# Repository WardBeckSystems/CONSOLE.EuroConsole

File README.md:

# EuroConsole

**A modular analog mixing console in Eurorack: Ward-Beck Systems circuits, digitally controlled, wired with Quad Twisted Pair.**

**Start here:** [`index.html`](index.html) walks through the whole console step by step. [`EDITOR/index.html`](EDITOR/index.html) builds your configuration as a KiCad schematic.

EuroConsole grows out of the 2016|49 *Digitally Controlled Analog Surround Sound Panner* (DCASSP), built at APK audio and Ward-Beck Systems as a Seneca College technology project. That prototype showed one idea: **the audio stays analog, the controls go digital**. Every control a mixer touches (encoders, buttons, faders, LEDs) is read by a microcontroller. The microcontroller sets digitally controlled analog parts, such as the Maxim DS1882 log-taper audio potentiometers, which do the actual work on the signal. Because the panel never carries audio, the controls can move, light up, recall and be driven remotely, and the signal path keeps the sound of the Ward-Beck circuits.

EuroConsole turns that prototype into a whole console, built from 3U Eurorack modules. The first build is the **C1616**:

| Part | What it is |
|---|---|
| **C1616 console** | 16 input channels (B300 Brain + F300 Fader strips) feeding **16 summing amplifiers**, in 4 rows of 6 modules |
| **Input** | M480B input module: the channel's mic/line front end |
| **4-input summing console** | one row: 4 × RJ45 QTP in (all 16 channels) → 4 summing amps, each with an insert point |
| **Processing** | EQ, compressor, de-esser, gate: patch into any insert |
| **Patch bay** | QTP patch bay module: inserts and buses on RJ45, normalled through |
| **Big VU Meter** (RD87) | the console's meter: the RD87 stereo Neopixel LED tower and its driver (REV 5, 2021\|54), plus moving-coil VU panels |

Everything connects with **QTP (Quad Twisted Pair)**: four balanced analog channels on one RJ45 / CAT5e cable, in the colour order **SUN, SKY, GRASS, EARTH**.

---

## How it fits together

```mermaid
flowchart LR
  subgraph CH["C1616: 16 channel strips"]
    direction TB
    B["B300 Brain<br/>input select · 4 aux · ESP32-S3"] --- F["F300 Fader<br/>POS pan · ONLY · SEL · fader · CH ON"]
  end
  IN["16 inputs<br/>(4 × QTP RJ45)"] --> M480["M480B input modules"] --> CH
  PB["QTP patch bay"] -.-|"normalled inserts and buses"| INS
  CH -->|"16 channels = 4 × QTP, to every row"| SUM
  subgraph SUM["Summing: 4 rows × (4 summing amps + insert + Big VU) = 16 summing amps"]
    direction TB
    Q["each row: 4 × RJ45 QTP in"] --> BUS["4 summing amps per row<br/>SUN · SKY · GRASS · EARTH"]
    BUS --> INS["insert point per bus<br/>send / return"]
  end
  INS <-->|"QTP send / return"| PROC
  subgraph PROC["Processing (any insert)"]
    direction TB
    EQ["EQ"] ~~~ COMP["Compressor"] ~~~ DES["De-esser"] ~~~ GATE["Gate"]
  end
  INS --> OUT["4 bus outputs (QTP)"]
  OUT --> DRV["Big VU Meter driver<br/>line in · MCU"] --> VU["Big VU Meter<br/>2 × 57 Neopixels"]
```

### Signal rules

- **Audio is analog and balanced end to end**: THAT 1246 line receivers in, THAT 1646 line drivers out. The 2016|49 prototype used these on every board.
- **Control is digital**: one ESP32-S3 per channel strip reads the panel and sets the gain parts. The modules talk to each other over I2C on the Eurorack bus, and the console talks to the outside world over the network. The 2016|49 prototype used Ethernet and the HUI protocol, run from an Arduino Mega.
- **Every interconnect is QTP**: one RJ45 carries four channels, so 16 outputs need only four cables. A QTP pair is also the insert send / return.

---

## 1. The C1616 console (16 × 16): channel strip = B300 + F300

**C1616** = 16 input channels × 16 summing amplifiers.

Each channel strip is two 6HP × 3U modules from the *HUI front panel REV 4.1* drawing ([DXF](MECHANICAL/HUI%20front%20panel%20REV%204.1.dxf)):

| B300 **Brain** (left) | F300 **Fader** (right) |
|---|---|
| INPUT LED and SEL button | **POS** encoder: position in the surround field (L · C · R · Ls · Rs) |
| SUN / SKY / GRASS / EARTH: four auxiliary controls, each with an encoder, a Neopixel and a push-button | **ONLY**: solo, isolate and cue |
| carries the channel's microcontroller | **SEL**: select, which draws attention to the channel |
| | 60 mm linear **fader** (Bourns PTA6043): channel level |
| | **CH ON**: channel on |

**Panning (from the 2016|49 theory of operation).** The POS encoder indexes a table of DS1882 settings, one per speaker, at 1 dB per step. Each speaker peaks at 63–64 steps, and neighbouring speakers cross at 48 steps (16 dB down):

```
{64,0,0,0,0} {48,48,0,0,0} {0,63,0,0,0} {0,48,48,0,0} {0,0,63,0,0} {0,0,48,48,0} {0,0,0,64,0} {0,0,0,48,48} {0,0,0,0,63}
```

The fader scales the looked-up row to a percentage. At power-up, every pot starts at full mute.

**C1616.** 16 input channels feed 16 summing amplifiers. The 16 channels leave the strips on four QTP cables (4 channels each), and every summing row receives all four. 16 strips × 12HP = 192HP, which is three rows of 84HP.

---

## 2. Summing: 4 rows of 6 = 16 summing amplifiers

The summing side is **4 rows of 6 modules**. Each row is one **4-input summing console**:

| Slot | Module |
|---|---|
| 1–4 | **summing amplifiers**: the row's four buses, SUN · SKY · GRASS · EARTH. All 16 channels arrive on the row's 4 × RJ45 QTP inputs |
| 5 | **insert / patch**: an insert send / return for each of the row's four buses (QTP) |
| 6 | **Big VU (RD87)**: meters the row's four buses |

4 rows × 4 = **16 summing amplifiers**: 16 inputs × 16 summing buses. Each bus has an **insert point** and leaves on a QTP output. *Slots 5 and 6 are provisional; the layout of 4 summing amps + 2 per row is set.* Big VU REV 5 shows two bars, so the row needs a 4-bar version, or two towers.

- **Summing amplifier:** Ward-Beck [M450](https://github.com/WardBeckSystems/MODULES.AMPLIFIERS.M450-Program-Summing-Amplifier) / [M450A](https://github.com/WardBeckSystems/MODULES.AMPLIFIERS.M450A-Program-Summing-Amplifier) / [M450B](https://github.com/WardBeckSystems/MODULES.AMPLIFIERS.M450B-Program-Summing-Amplifier) program summing amplifiers (Rodger Beck, 1975|8–1979|12). The 2016|49 prototype summed through 2 × 4 M450A cards. Also [M484 Dual Summing Amplifier](https://github.com/WardBeckSystems/MODULES.SUMMING.M484-Dual-Summing-Amplifier).
- **QTP backplane:** **QTP-BAC 14.1** (in `KICAD/`) is the four-channel QTP board, with RJ45s, transformers, XLR and BNC for SUN/SKY/GRASS/EARTH. It is the starting point for the summing console's input/output board.
- **Insert points:** a balanced send and return per bus, switched in or out. The model is the [M499 Insertion Switcher](https://github.com/WardBeckSystems/MODULES.UNSORTED.M499-Insertion-Switcher), plus the 1979|12 *M466N Insert Meter Module* drawing ([M466](https://github.com/WardBeckSystems/MODULES.DYNAMICS.M466-Limiter-Compressor-Module)). *Proposed:* sends on one RJ45 and returns on another, with QTP pairs 1–4 = buses 1–4, so one cable pair inserts a processor into all four buses.

---

## 3. Input: M480B

The [M480B input module](EAGLE/2021-APK/M480B%20Input%20module.sch) is the channel front end ahead of the B300/F300 strip. APK redrew it in Eagle in 2021|54 from the Ward-Beck original: LM201 op-amps, a MAT-01 matched pair and discrete output transistors (255 parts).

## 4. Processing: EQ, compressor, de-esser, gate

Each processor is a Eurorack module with QTP send / return, so it patches into any insert. Each one starts from a Ward-Beck circuit already drawn in this archive. Three already exist as 2021|54 APK Eagle redraws in [EAGLE/2021-APK](EAGLE/2021-APK/):

| Function | Starting from | Eagle (2021\|54 APK) | KiCad in the archive |
|---|---|---|---|
| **EQ** | [M462B Effects Equalizer](https://github.com/WardBeckSystems/MODULES.FILTERS.M462B-Equalizer-Module); also [M462](https://github.com/WardBeckSystems/MODULES.FILTERS.M462-Equalizer-Module), [M472](https://github.com/WardBeckSystems/MODULES.FILTERS.M472-Equalizer-Module) / [M472A](https://github.com/WardBeckSystems/MODULES.FILTERS.M472A-Stereo-Equalizer-Module) | `M462B Final.sch` (356 parts) | M462 27 · M462B 10 · M462C 11 · M472 14 · M472A 7 sheets |
| **Compressor** | [M466 Limiter-Compressor](https://github.com/WardBeckSystems/MODULES.DYNAMICS.M466-Limiter-Compressor-Module) (1976\|9): signal path, 6-106 control amplifier, output amplifier | `M466-compressor-limiter.sch` (315), `M466 - Control amp.sch` (114) | M466 15 · [M466M](https://github.com/WardBeckSystems/MODULES.DYNAMICS.M466M-Compressor-Meter-Module) 3 |
| **Output amplifier** (EQ and compressor) | the M466 / M462B output stage: LM201 and 4 complementary pairs | `M466 and M462B Output Amplifier.sch` (87) | in M466 |
| **De-esser** | M466 with a frequency-weighted (high-pass / band-pass) side-chain into its control amplifier | — | new circuit, based on M466 |
| **Gate** | [M467 Noise Gate and Meter Module](https://github.com/WardBeckSystems/MODULES.DYNAMICS.M467-Noise-Gate-and-Meter-Module) | — | M467 8 |

The front panels follow the B300/F300 language: encoders with Neopixels and POD buttons. The processor's ESP32-S3 sets its thresholds and gains through digitally controlled parts.

## 5. Patch bay

The **QTP patch bay module** puts every insert send / return and bus on RJ45, normalled through, so processors patch in with one CAT cable per four channels. It starts from **QTP-BITTREE PATCHBAY REV 2.1** (2021|54, Gerbers marked "good to go"): a 34 × 41 mm card with a top-row and bottom-row QTP RJ45, plugging into a Bittree patchbay connector, so a Bittree bay becomes a QTP bay. A sibling, **QTP-NEUTRIK D-hole** (24 × 27 mm), mounts a QTP RJ45 in a standard Neutrik D-hole for panels.

## 6. Metering: the Big VU Meter (RD87)

Big VU is Ward-Beck R&D project **RD87**, the *RD87 LED tower* (2015|48): a free-standing stereo level tower. Product repo: [PRODUCTS.BigVU](https://github.com/WardBeckSystems/PRODUCTS.BigVU). Page: [WBSps.ca Big VU](https://WBSps.ca/2026/PAGES/Big-VU.html). Simulator: [Big VU](https://WBSps.ca/2026/siumulation.html?plugin=bigvu), with front panel, tutorial, block diagram and firmware trace. In EuroConsole it is the console's meter bridge: one tower per bus pair, fed from the bus outputs.

- **VU meter driver + meter: Big VU Meter REV 5** (2021|54, 102 × 64 mm). A dual op-amp line input feeds an Arduino Micro, which drives two Neopixel bars of 57 pixels each (left / right). Two WBS 10-080 pots set the ceiling. The firmware ([SOFTWARE/BigVU](SOFTWARE/BigVU/), 2015|48) adds a log scale, calibration and two falling peak dots. This is the driver to move to Eurorack and the ESP32-S3.
- **Moving-coil VU meters**, one per bus, as in the 2016|49 prototype (five WBS meters, each with a 15 dB calibration pad): [M435 VU Meter](https://github.com/WardBeckSystems/MODULES.METER.M435-VU-Meter), driven by an [M405 Extended Range VU Meter](https://github.com/WardBeckSystems/MODULES.METER.M405-Extended-Range-VU-Meter) / [M445](https://github.com/WardBeckSystems/MODULES.METER.M445-Extended-Range-Meter) stage (+4 dBu = 0 VU).

---

## Console editor: configuration → KiCad schematic

[`EDITOR/index.html`](EDITOR/index.html) is an interactive page that builds a specific console and writes its KiCad 9 schematic. Open it in a browser; it works offline from the file.

- **Every Eurorack module is a bank of 4 channels** (one QTP in / out): quad preamp (4 preamp sections + 4 vertical VU), EQ, compressor, de-esser, send banks and faders, 24HP, drawn to Eurorack scale with the master section in the middle.
- **Summing in the send banks:** each send bank (Aux 1-4, Aux 5-8, M 1-4) takes two 4-channel inputs, PRE (the insert return, before the fader) and POST (the fader out), sets every send pre or post, sums its 4 channels per bus inside the module with the bus coming in from the previous bank, and passes the bus on to the next bank, then the master (insert, compressor, fader, Big VU). No summing point takes more than 5 inputs. Every bank also has a pre-fader and a post-fader QTP out. Separate summing amps are set aside for now.
- **Digitally controlled analog:** every parameter is a DS1882 wiper or a digital switch under a control layer (an ESP32-S3 per bank on I2C). The editor counts the parameters, DS1882s, I2C expanders and I2C buses.
- **Power:** a first estimate per module on +12 V, −12 V and +5 V, per rack row and in total, with the supplies needed and a power-flow diagram (to be measured).
- **Summing rows:** each summing amp is a bus named by what it sums: M1–M4, AUX1–AUX8, then direct sums (BUS13…). The C1616 is rows M1–4 · AUX1–4 · AUX5–8 · BUS13–16, each with insert and Big VU. The name follows the configuration: 16 inputs × 16 summing amps = **C1616**.
- **Download:** a zip of a hierarchical KiCad 9 project: a root sheet, a channels sheet and one sheet per summing row. It includes `EuroConsole.kicad_sym` and `sym-lib-table`, plus the configuration (JSON, which *Load config* reads back) and a parts list (CSV).
- **Symbols:** the Ward-Beck modules use the archive's own symbols (`2026/Engineering/KICAD`: M480B, M450, M499, M462B, M466, M467), with their real card-edge pins. QTP RJ45, XLR, the B300/F300 strip and the RD87 Big VU are EuroConsole parts. Run `python3 EDITOR/build_symbols.py` to refresh `symbols.js`.
- **Nets** are global labels shared by every sheet: `IN` (XLR), `FS`/`FR` (M480B fader send / return through the strip), `CH` (channels on QTP), `SUMN` (summing nodes), `SEND`/`RET` (inserts), `BUS` (bus outputs) and `P<ref>_` (processor patch points). QTP pairs are SUN 2/1 · SKY 4/5 · GRASS 6/3 · EARTH 8/7, with the shell to GND.
- **Tested:** `node EDITOR/test_generator.js` generates the C1616, has `kicad-cli` load it, and checks the netlist. Each summing node has its 16 resistors plus the M450 input; each channel reaches its 16 resistors and all four rows. ERC leaves only "power pin not driven" (the schematic has no supply). The archive's M462B, M466 and M467 symbols give left and right the same pin numbers, so ERC reports duplicate pins when those modules are placed.

## Reference: Boredbrain Xcelon

The [Boredbrain Music Xcelon](https://www.chicagomusicexchange.com/en-ca/blogs/news/boredbrain-music-xcelon-eurorack) (CA$1,372) is the closest commercial Eurorack mixer: an all-analog six-channel stereo mixer in one module. Its features, against EuroConsole:

| Xcelon | EuroConsole |
|---|---|
| Six stereo / dual-mono channels, low-noise analog | banks of 4 mono channels per module; balanced +4 dBu on QTP; Ward-Beck circuits |
| Two stereo FX sends, two FX returns | Aux 1-4 and Aux 5-8 send banks (8 sends); returns through the insert / patch bay |
| Two stereo mix buses, selectable per channel | M 1-4 send bank onto the M1-M4 masters; direct sums |
| Variable input gain for modular and line-level sources | quad preamp (M480 / M460 / M470 / M441): mic or line; **planned:** a Eurorack-level input setting |
| Long-travel faders with CV-responsive LEDs | F300 fader bank (60 mm Bourns) with Neopixels |
| Balance with pan law; dual-mono crossfade mode | F300 POS pan on the DS1882 pan-law table; **planned:** crossfade mode |
| Clickless mutes, VU meters on all channels | CH ON; the DS1882's zero-crossing detector switches without clicks; quad preamp meters and Big VU on every bus |
| 26 CV inputs | **planned:** CV in per channel (volume 0 to +5 V, pan ±5 V, sends), read by the bank's ESP32-S3 |
| Jumpers: pre/post-fader FX and meters, volume VCA mode | send taps are post-fader (in software, settable per bank, **planned**); every level is a DS1882, so a VCA mode is a firmware setting |
| Expansion ports: channel expanders, direct outs | every bank is a module; every channel already leaves on QTP (direct out) |

## Reference: XAOC Devices Praga

The **XAOC Devices Praga** (*1967 Voltage Controlled Stereo Mixing Console*) is a Eurorack mixer laid out the way EuroConsole lays out every module: **a bank of 4 channels in one module**. From its front panel, each channel has a large VOL knob, an ACTIVE / MODE button with a status LED, PAN, an AUX knob between sends A and B, a **5-segment vertical LED meter**, and jacks for INPUT, VCA OUT and PAN / VOL CV; the shared row carries AUX SEND / RETURN A and B and the STEREO SUM L / R.

| Praga | EuroConsole |
|---|---|
| 4 channels per module | every module is a bank of 4 channels (24HP, one QTP in and out) |
| a vertical LED meter per channel | the quad preamp's vertical VU per channel; Big VU on every bus |
| PAN and VOL CV per channel | **planned** (see the Xcelon: CV in, read by the bank's ESP32-S3) |
| AUX knob between sends A and B | the send banks: Aux 1-4, Aux 5-8, M 1-4 |
| VCA OUT per channel | every channel leaves on QTP (direct out) |
| stereo sum on the module | summing stays in its own modules: group sums of 8 with their channels, the Σ in the master |

## Reference: WMD Performance Mixer MKII

The **WMD Performance Mixer MKII** (US$2,205; PM Channels MKII US$955, PM DB25 MKII US$440, PM MKII Returns US$205) is the most console-like of the three: eight stereo channels, expanding **four channels at a time** up to 24.

| Performance Mixer MKII | EuroConsole |
|---|---|
| Expands 4 channels at a time (PM Channels MKII), up to 24 | every module is a bank of 4; channels in fours, 4 to 64 |
| DB25 MKII: balanced line-level outs, pre- or post-fader, per 4 channels | every bank leaves on QTP (4 balanced channels per RJ45); **planned:** pre / post choice |
| Gain −12 to +20 dB, clip LED 1 dB before clipping | quad preamp gain; **planned:** a clip LED per channel |
| Soft mute (no click) | CH ON through the DS1882's zero-crossing switch |
| Pan or crossfade per channel; CV sums with the pot | F300 POS pan; **planned:** crossfade mode and CV in |
| Faders as VCAs (Level CV in VCA mode) | every level is a DS1882 set by the ESP32-S3: a VCA mode is firmware |
| AUX1 post, AUX2 pre or post | Aux 1-4 / Aux 5-8 send banks, post-fader; **planned:** pre / post per bank |
| Cue and Bus: master only, master + bus, bus only | ONLY (solo / cue) on the F300; M 1-4 send bank onto the M1-M4 masters |
| Groups: 8 mute / bus / cue snapshots recalled with one hand | **planned:** snapshots in the ESP32-S3s (the controls are all digital already) |
| Master insert; Mix In after the insert; Aux returns before it | insert on every master bus (M499 + QTP send / return); **planned:** a Mix In after the master insert |
| Balanced stereo master out, LED VU | QTP bus outs; Big VU on every bus |
| Replaceable channel strips; patchbay, power and master as separate assemblies | every bank module is replaceable by itself |
| Expansion headers 2.0 mm shrouded, cannot be plugged into power | **planned:** keyed inter-module connectors that cannot meet the Eurorack 16-pin power |

**From the manual** (WMD, *Performance Mixer MKII*):

| | Performance Mixer MKII | PM Channels MKII (4 ch) | DB25 MKII |
|---|---|---|---|
| Width | 52HP | **24HP** | 4HP |
| Power | +620 / −560 mA (to ±750 mA when distorting) | +320 / −280 mA (to ±350 mA) | ±150 mA |
| Inputs | 20 kΩ; HPF −3 dB at 10 Hz; gain −12 to +20 dB | same | — |
| Faders / aux | −100 to +5 dB; level / aux CV 0 to 5 V (100 kΩ); pan CV ±5 V (200 kΩ) | same | — |
| Outputs | master balanced 3.5 mm TRS, 600 Ω, DRV135; others 1 kΩ modular level | 1 kΩ modular level | 16 × DRV135, balanced 600 Ω, **+4 dBu nominal**, THD+N < 0.1 %, TASCAM DB25 |
| Pan law | −3 dB centre, −100 / 0 dB hard pan | same | — |
| Response | ±0.5 dB 20 Hz–20 kHz; L/R within ±0.5 dB; every point phase-correct | same | — |

Also from the manual:
- Each OUTS header is 2 mm, 16-pin: four stereo channels, signal on the even pins and ground on every odd pin.
- Each INSERT header is 8-pin: send / return left and right, post-gain and pre-fader, with jumpers when unused.
- MIDI: CC 32 upward, 4 per strip (level, pan, aux 1, aux 2).
- 8 group snapshots of mute, bus and cue.
- Firmware loads from an SD card.

**What it tells EuroConsole:**
- **Width:** a bank of 4 at 24HP is what WMD ships for 4 channels (PM Channels MKII).
- **Power:** about +320 / −280 mA per 4-channel module is a realistic budget to check our banks against on ±12 V.
- **Balanced outs:** WMD's DB25 uses DRV135 drivers at +4 dBu. Our THAT 1646 drivers do the same job on QTP.
- **Internal ribbons:** ground on every other conductor between modules.
- **Inserts:** an insert point on every channel, post-gain and pre-fader, beside the master insert.
- **Firmware:** the ESP32-S3s can send the same kind of MIDI CC overlay for DAW automation, and keep group snapshots.

## Boards in this repo

`KICAD/` holds KiCad 9 boards converted from the Eagle designs in `EAGLE/` with [`tools/eagle2kicad_pcb.py`](https://github.com/WardBeckSystems/WBSps.ca/blob/main/tools/eagle2kicad_pcb.py). `KICAD/split_boards.py` splits the combined 2016|49 Eagle sheet into one board per module. Each board is placed in its panel's coordinates, with the panel drawing on *User.Drawings*.

| Board | From | Size | Parts | Panel check |
|---|---|---|---|---|
| `B300_Front` | 2016\|49 Encoder PCB 17.2 | 30 × 113.6 mm | 37 | all 14 controls within 0.18 mm of their panel holes (4 Neopixels + INPUT LED, 4 encoder holes, 5 buttons) |
| `F300_Fader` | 2016\|49 Encoder PCB 17.2 | 30 × 113.6 mm, L-shape | 14 | ONLY, SEL and CH ON within 0.01 mm; the fader's 4 mounting pads within 0.02 mm of the panel screws; the POS encoder mounts on the panel above the notch |
| `B300_Main` | 2016\|49 Encoder PCB 17.2 | 133.8 × 113.4 mm | 27 | perpendicular side board: 4 encoders (WBS 10-081), Arduino Mega, RS-485, DB9, DS1808 |
| `Maxim_Adapter_Board` | 2016\|49 Maxim Adapter Board | 20 × 25 mm | 3 | DS1882 breakout (also on the Encoder sheet) |
| `QTP-BAC_14.1` | 2016\|49 | 114 × 50 mm | 112 | four-channel QTP backplane: RJ45, transformers, XLR, BNC |
| `Big_VU_Meter_REV5` | 2021\|54 APK | 102 × 64 mm | 84 | stereo Neopixel VU meter and driver |
| `QTP-BITTREE_Patchbay_REV2.1` | 2021\|54 APK | 34 × 41 mm | 10 | QTP card for a Bittree patchbay |
| `QTP-NEUTRIK_D-hole` | 2021\|54 APK | 24 × 27 mm | 7 | QTP RJ45 in a Neutrik D-hole |
| `Encoder_PCB_17.2` | 2016\|49 | — | 221 | the whole Eagle sheet, kept as the source |

| B300 Front | F300 Fader | Big VU Meter | QTP Bittree patchbay |
|---|---|---|---|
|  |  |  |  |

**Schematics.** The Eagle `.sch` files (M480B, M462B, M466, the output amplifier, the VU meter, the patchbay, and the 2016|49 DCASSP sheets) still need KiCad's GUI importer: File → Import → Non-KiCad Schematic. The 2016|49 schematics are also in [MANUALS/2016 - DCASSP schematics V1.pdf](MANUALS/2016%20-%20DCASSP%20schematics%20V1.pdf).

## Roadmap

- **From the Xcelon, the Praga and the WMD Performance Mixer MKII:** CV inputs per channel (volume, pan, sends) read by each bank's ESP32-S3; a Eurorack-level input setting and a clip LED per channel on the quad preamp; pan crossfade mode; pre / post-fader sends and direct outs per bank; mute / bus / cue snapshots; a Mix In after the master insert; keyed inter-module connectors that cannot meet power.

1. **B300 / F300 for Eurorack**: replace the Arduino Mega side board with an ESP32-S3 on the B300, and connect the F300 by ribbon. Use the Eurorack 16-pin power header (±12 V, regulated to ±7 V for the DS1882 analog rails). Connect modules over I2C.
2. **Input**: M480B as a Eurorack input module.
3. **Summing console**: a 4 × QTP input board from QTP-BAC, an M450-style summing amplifier per bus, and an insert send / return per bus.
4. **Processing**: EQ (M462B), compressor (M466), de-esser (M466 side-chain), gate (M467). Each gets a Eurorack PCB and panel with QTP send / return, sharing the M466/M462B output amplifier.
5. **Patch bay**: QTP-BITTREE and QTP-NEUTRIK into a Eurorack QTP patch module, normalled.
6. **Metering**: Big VU Meter onto the ESP32-S3 as the VU meter driver, plus moving-coil VU panels.
7. **The C1616 frame**: three 84HP rows, the power, the QTP patch, and network control.

## Source material

| Folder | What |
|---|---|
| [EAGLE/2016-DCASSP](EAGLE/2016-DCASSP/) | Encoder PCB 17.2, QTP-BAC 14.1, Maxim (DS1882) adapter, VU meter and summing amp, block diagram |
| [EAGLE/2021-APK](EAGLE/2021-APK/) | M480B, M462B, M466, M466 control amp, M466/M462B output amp, Big VU Meter REV 5, QTP-BITTREE patchbay, QTP-NEUTRIK D-hole |
| [GERBERS/](GERBERS/) | QTP-BITTREE PATCHBAY REV 2.1 ("good to go") |
| [SOFTWARE/](SOFTWARE/) | DCASSP channel-strip firmware (Arduino Mega, 2016) with its history, pan law and PC interface; Big VU meter firmware (all versions), which runs every vertical meter |
| [MANUALS/](MANUALS/) | 2016\|49 DCASSP final report (TPJ655) and schematics |
| [MECHANICAL/](MECHANICAL/) | HUI front panel REV 4.1 (DXF and render), Bourns PTA6043 fader |
| [PHOTOS/](PHOTOS/) | HUI prototype cross reference |

---
© Ward-Beck Systems (Ward-Beck.com - Ward-Beck.ca) · DCASSP design and archive by Anthony Peter Kuzub · [WBSps.ca](https://WBSps.ca) · [WBSps.Kuzub.com](https://WBSps.Kuzub.com)

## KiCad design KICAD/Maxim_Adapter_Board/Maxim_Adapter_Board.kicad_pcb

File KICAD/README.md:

# EuroConsole boards (KiCad 9)

| Board | Rev | What it is | From |
|---|---|---|---|
| [B300 Brain - front PCB](B300_Front/) | 17.2 | Neopixels, POD buttons, encoder shaft holes; placed on the HUI front panel REV 4.1 | Encoder PCB REV 17.2 (2016 DCASSP) |
| [B300 Brain - main side board](B300_Main/) | 17.2 | 4 encoders (WBS 10-081), Arduino Mega, RS-485, DB9, DS1808; perpendicular to the panel | Encoder PCB REV 17.2 (2016 DCASSP) |
| [F300 Fader - fader PCB](F300_Fader/) | 17.2 | Bourns PTA6043 fader, ONLY / SEL / CH ON buttons; placed on the HUI front panel REV 4.1 | Encoder PCB REV 17.2 (2016 DCASSP) |
| [DS1882 adapter](DS1882_Adapter/) | 17.2 | Maxim DS1882 dual log digital potentiometer breakout | Encoder PCB REV 17.2 (2016 DCASSP) |
| [QTP-BAC - four-channel QTP backplane](QTP-BAC_14.1/) | 14.1 | SUN SKY GRASS EARTH on RJ45: transformers, XLR, BNC, euro blocks | QTP-BAC 14.1 (2016 DCASSP) |
| [Big VU (RD87) - meter and driver](Big_VU_Meter_REV5/) | 5 | stereo line in, Arduino Micro, 2 x 57 Neopixel towers | Big VU meter REV 5 (2021 APK) |
| [QTP-BITTREE - patchbay card](QTP-BITTREE_Patchbay_REV2.1/) | 2.1 | top-row and bottom-row QTP RJ45 on a Bittree patchbay connector | QTP-BITTREE PATCHBAY REV 2.1 (2021 APK) |
| [QTP-NEUTRIK - D-hole RJ45](QTP-NEUTRIK_D-hole/) | 1 | QTP RJ45 in a Neutrik D-hole | QTP-NEUTRIK D-hole (2021 APK) |
| [Encoder PCB - 2016 DCASSP sheet (source)](Encoder_PCB_17.2/) | 17.2 | the whole Eagle sheet: every board above plus documentation frames | Encoder PCB REV 17.2 (2016 DCASSP) |

Each board carries its name in the title block. `split_boards.py` splits the Encoder sheet per module in panel coordinates; `name_boards.py` writes these names.

## Schematics

Every Eagle schematic in `EAGLE/` is converted with KiCad's own importer (eeschema, File → Import → Non-KiCad Schematic), driven on a virtual display because `kicad-cli` has no schematic import: `tools/eagle_sch_batch.py` (Xvfb `:77`, a fresh eeschema per file; `xdrv.py` clicks / keys, `xclip_owner.py` hands the path to the file dialog). Each converted schematic sits next to its board where there is one, with its `*-eagle-import.kicad_sym` and `sym-lib-table`.

| Schematic | Parts | Nets |
|---|---|---|
| Encoder_PCB_17.2 (11 sheets) | 173 | 278 |
| M462B_EQ | 268 | 224 |
| M466_Compressor_Limiter | 231 | 191 |
| M480B_Input_Module | 205 | 187 |
| M466_Control_Amp | 82 | 60 |
| Big_VU_Meter_REV5 | 80 | 79 |
| M466_M462B_Output_Amplifier | 73 | 50 |
| QTP-BAC_14.1 | 68 | 43 |
| VU_Meter_Summing_Amp_rev1 | 22 | 59 |
| QTP-BITTREE_Patchbay_REV2.1 | 10 | 45 |
| QTP-NEUTRIK_D-hole | 8 | 17 |
| Block_Diagram_v2 | 6 | 10 |
| Maxim_Adapter_Board | 3 | 16 |

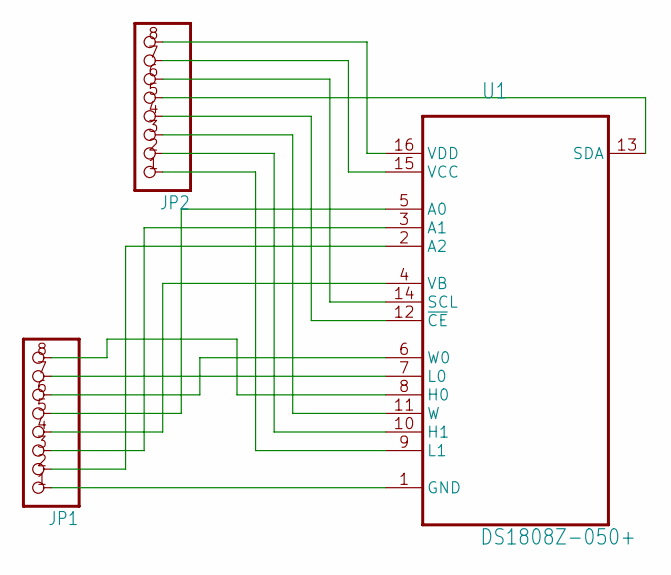
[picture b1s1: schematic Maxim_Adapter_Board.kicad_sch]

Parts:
JP1, JP2: PINHD-1X8; 1X08
U1: DS1808Z-050+; SOIC127P600X175-16N

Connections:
unnamed: JP1.1, U1.1 (GND)
unnamed: JP1.2, U1.2 (A2)
unnamed: JP1.3, U1.3 (A1)
unnamed: JP1.4, U1.4 (VB)
unnamed: JP1.5, U1.5 (A0)
unnamed: JP1.6, U1.6 (W0)
unnamed: JP1.7, U1.7 (L0)
unnamed: JP1.8, U1.8 (H0)
unnamed: JP2.1, U1.9 (L1)
unnamed: JP2.2, U1.10 (H1)
unnamed: JP2.3, U1.11 (W)
unnamed: JP2.4, U1.12 (~CE)
unnamed: JP2.5, U1.13 (SDA)
unnamed: JP2.6, U1.14 (SCL)
unnamed: JP2.7, U1.15 (VCC)
unnamed: JP2.8, U1.16 (VDD)

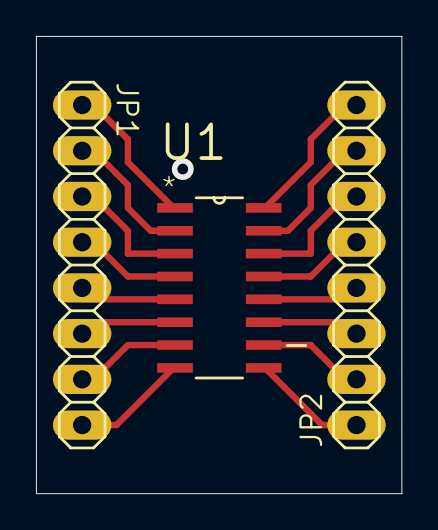
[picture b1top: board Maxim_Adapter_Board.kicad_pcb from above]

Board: 2 copper layers, 20.3 x 25.4 mm, 3 parts (0 on the bottom side), 16 nets.

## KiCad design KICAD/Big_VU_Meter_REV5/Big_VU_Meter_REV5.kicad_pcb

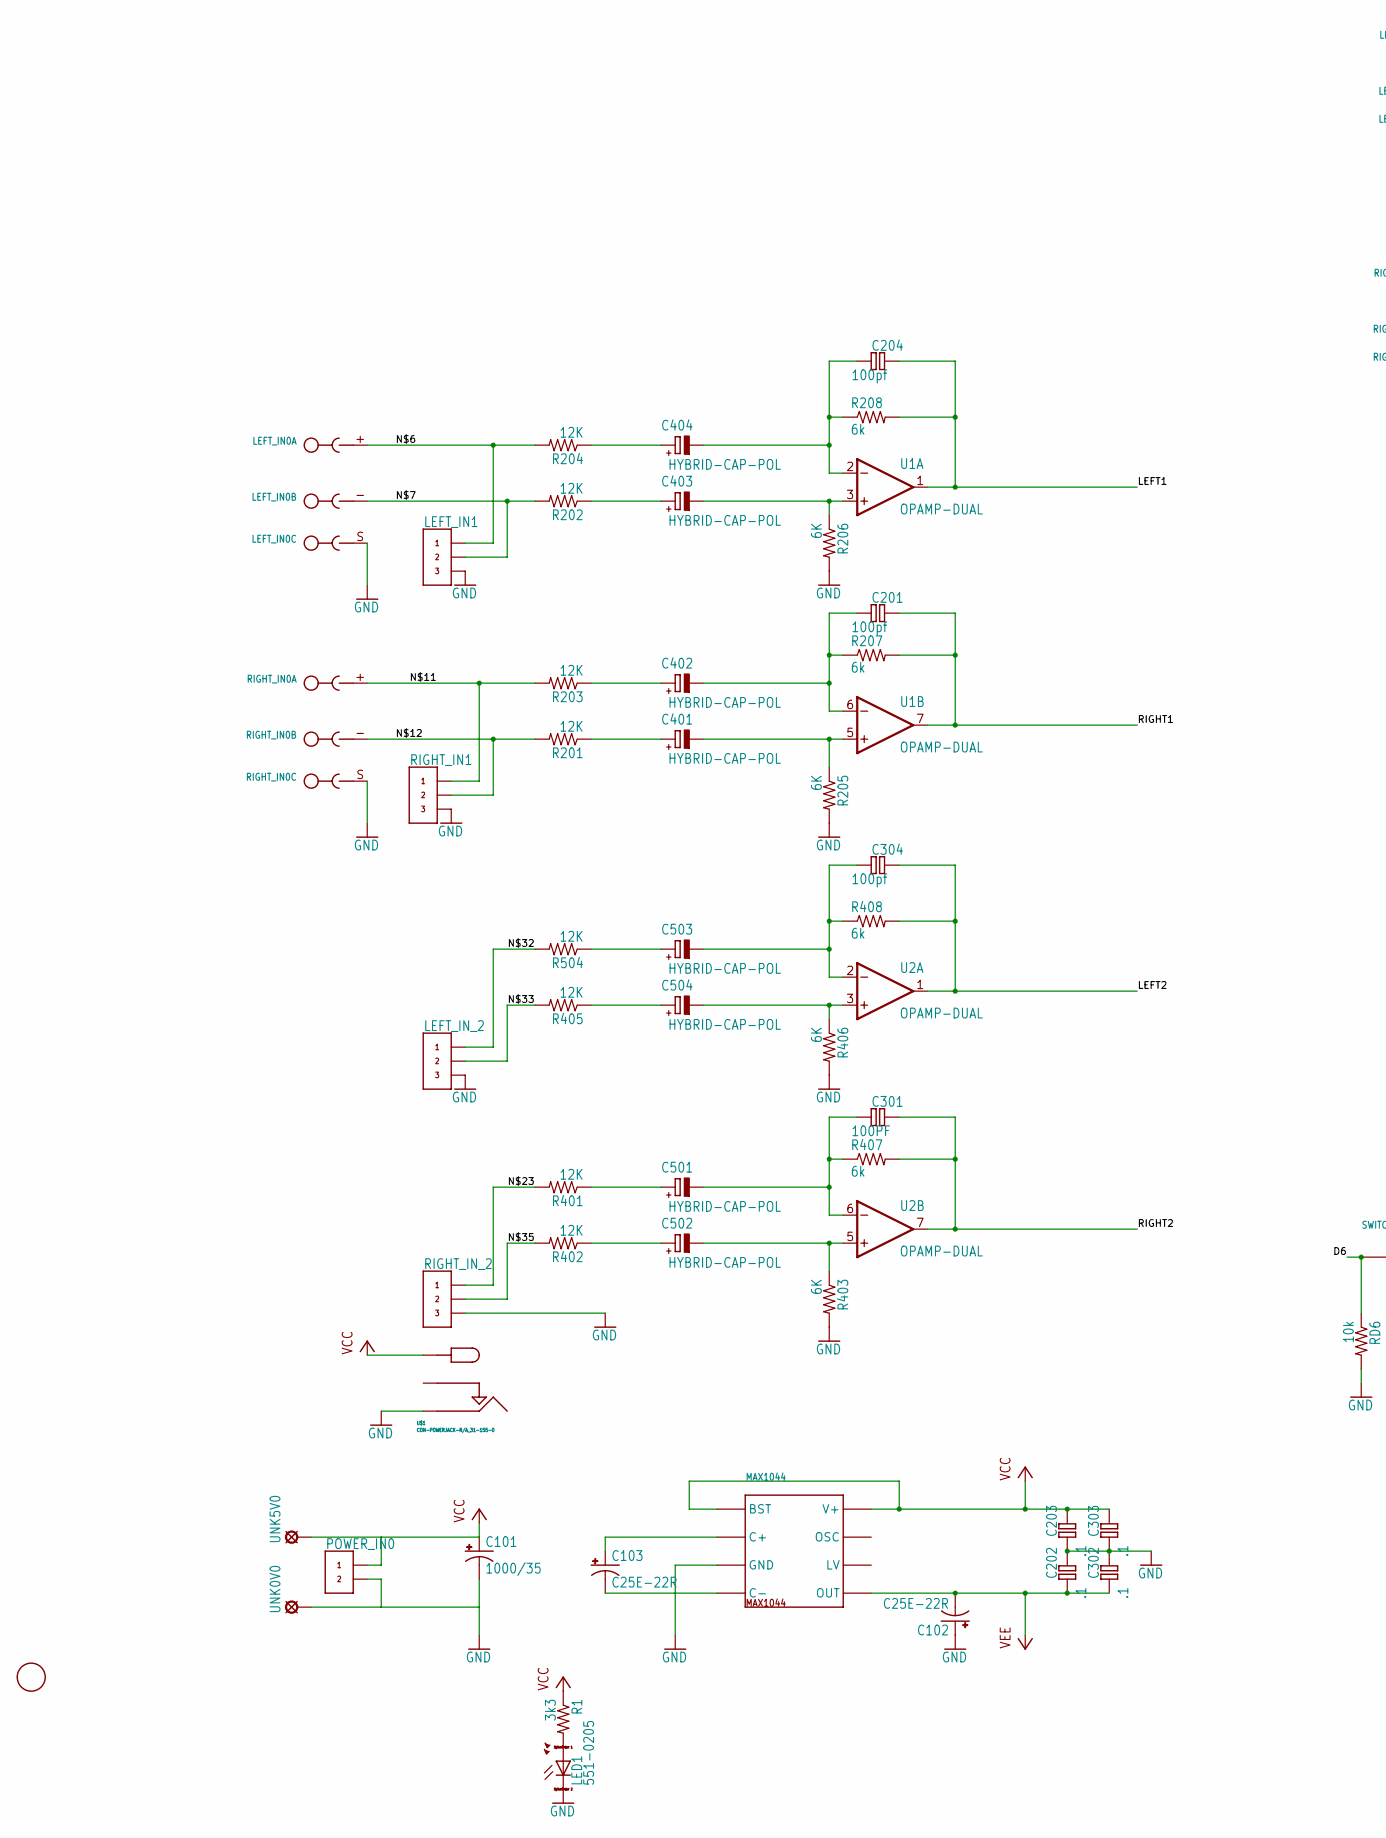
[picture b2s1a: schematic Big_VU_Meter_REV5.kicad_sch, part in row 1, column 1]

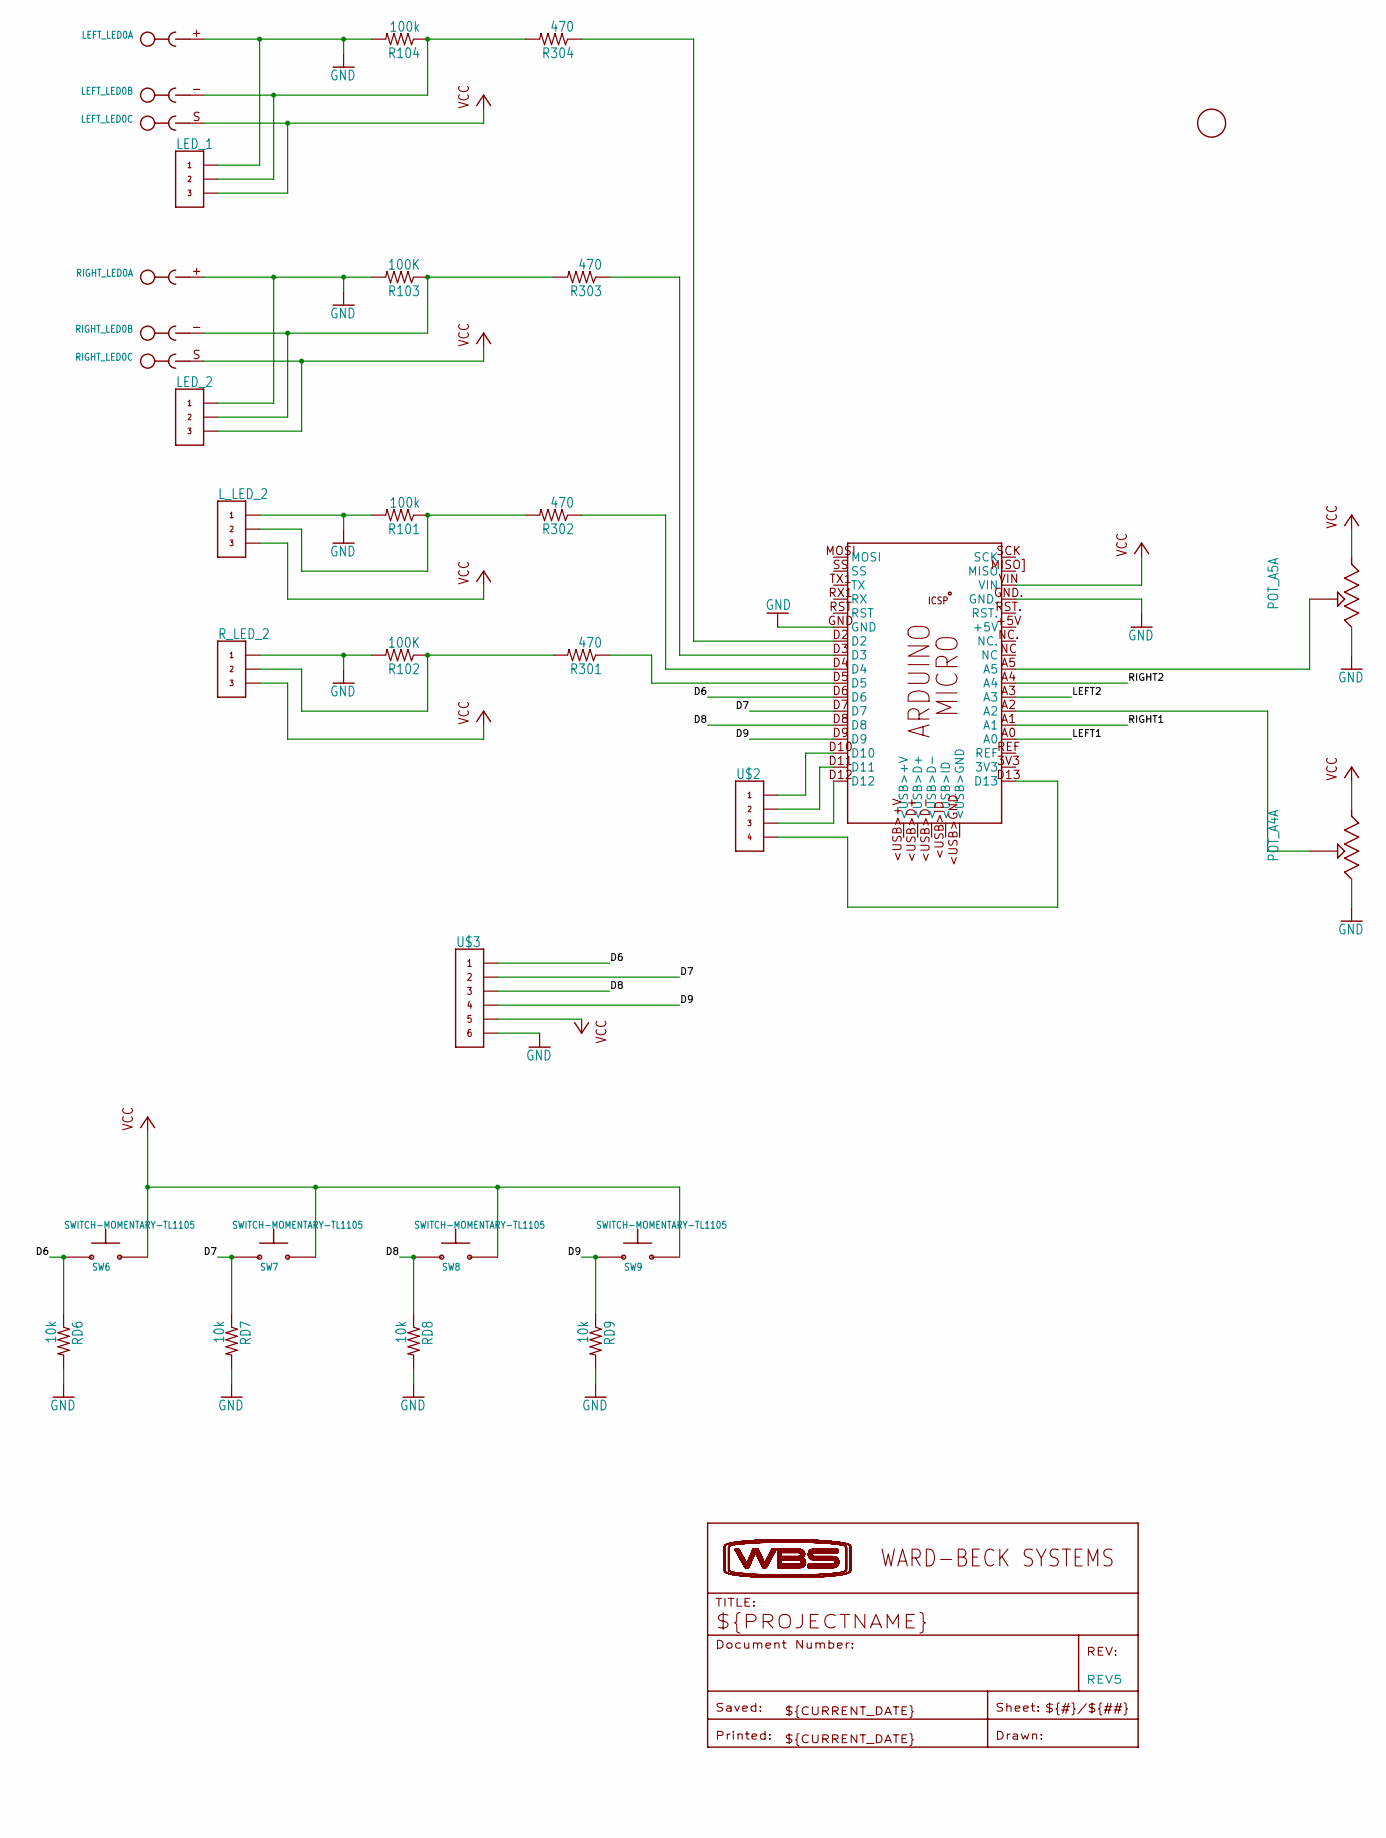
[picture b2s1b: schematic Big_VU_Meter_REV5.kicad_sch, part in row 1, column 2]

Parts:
C101: 1000/35; E5-5
C102, C103: C25E-22R; E2,5-6
C201, C204, C304: 100pf; HYBRID-CAP-CERAMIC-1206
C202, C203, C302, C303: .1; HYBRID-CAP-CERAMIC-1206
C301: 100PF; HYBRID-CAP-CERAMIC-1206
C401, C402, C403, C404, C501, C502, C503, C504: HYBRID-CAP-POL; HYBRID-CAP-TANT
LED1: 551-0205; LED_LD260
LED_1, LED_2: CON-WBS-LOCKING-0.1-3
LEFT_IN0: CON-PHOENIX_RIGHT_ANGLE_3.81; CON-PHOENIX_MC1.5_3-G-3.81
LEFT_IN1: CON-WBS-LOCKING-0.1-3
LEFT_IN_2: CON-WBS-LOCKING-0.1-3
LEFT_LED0: CON-PHOENIX_RIGHT_ANGLE_3.81; CON-PHOENIX_MC1.5_3-G-3.81
L_LED_2: CON-WBS-LOCKING-0.1-3
MAX1044: MAX1044; DIP8
PCB1: ARDUINO_MICRO
POT_A4, POT_A5: 10-080; WBS_079
POWER_IN0: CON-WBS-LOCKING-0.1-2
R1: 3k3; HYBRID-RESISTOR-1206-0.3
R101, R104: 100k; HYBRID-RESISTOR-1206-0.3
R102, R103: 100K; HYBRID-RESISTOR-1206-0.3
R201, R202, R203, R204, R401, R402, R405, R504: 12K; HYBRID-RESISTOR-1206-0.3
R205, R206, R403, R406: 6K; HYBRID-RESISTOR-1206-0.3
R207, R208, R407, R408: 6k; HYBRID-RESISTOR-1206-0.3
R301, R302, R303, R304: 470; HYBRID-RESISTOR-1206-0.3
RD6, RD7, RD8, RD9: 10k; HYBRID-RESISTOR-1206-0.3
REV5: WBS-DOCUMENT_INFO_FRAME; WBS-FRAME_PCB
RIGHT_IN0: CON-PHOENIX_RIGHT_ANGLE_3.81; CON-PHOENIX_MC1.5_3-G-3.81
RIGHT_IN1: CON-WBS-LOCKING-0.1-3
RIGHT_IN_2: CON-WBS-LOCKING-0.1-3
RIGHT_LED0: CON-PHOENIX_RIGHT_ANGLE_3.81; CON-PHOENIX_MC1.5_3-G-3.81
R_LED_2: CON-WBS-LOCKING-0.1-3
SW6, SW7, SW8, SW9: SWITCH-MOMENTARY-TL1105; SWITCH-TACT_TL1105
U1, U2: OPAMP-DUAL; DIP8
U$1: CON-POWERJACK-R/A_31-155-0; CON-POWERJACK-R_A_31-155-0
U$2: CON-WBS-LOCKING-0.1-4
U$3: CON-WBS-LOCKING-0.1-6
U$4, U$5: FIDUCIAL; FIDUCIAL_1MM
UNK0V0, UNK5V0: LSP13

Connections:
D6: PCB1.D6, RD6.1, RD6.1A (1), SW6.P$1 (1), SW6.P$2 (1), U$3.P$1
D7: PCB1.D7, RD7.1, RD7.1A (1), SW7.P$1 (1), SW7.P$2 (1), U$3.P$2
D8: PCB1.D8, RD8.1, RD8.1A (1), SW8.P$1 (1), SW8.P$2 (1), U$3.P$3
D9: PCB1.D9, RD9.1, RD9.1A (1), SW9.P$1 (1), SW9.P$2 (1), U$3.P$4
D10: PCB1.D10, U$2.P$1
D11: PCB1.D11, U$2.P$2
D12: PCB1.D12, U$2.P$3
D13: PCB1.D13, U$2.P$4
GND: C101.-, C102.+, C202.2 (-), C202.B2 (-), C203.1 (+), C203.A1 (+), C302.2 (-), C302.B2 (-), C303.1 (+), C303.A1 (+), LED1.K (C), LED_1.P$1, LED_2.P$1, LEFT_IN0.S, LEFT_IN1.P$3, LEFT_IN_2.P$3, LEFT_LED0.+, L_LED_2.P$1, MAX1044.P$3 (GND), PCB1.GND, PCB1.GND., POT_A4.P$3 (CW), POT_A5.P$3 (CW), POWER_IN0.P$2, R101.2, R101.2A (2), R102.2, R102.2A (2), R103.2, R103.2A (2), R104.2, R104.2A (2), R205.2, R205.2A (2), R206.2, R206.2A (2), R403.2, R403.2A (2), R406.2, R406.2A (2), RD6.2, RD6.2A (2), RD7.2, RD7.2A (2), RD8.2, RD8.2A (2), RD9.2, RD9.2A (2), RIGHT_IN0.S, RIGHT_IN1.P$3, RIGHT_IN_2.P$3, RIGHT_LED0.+, R_LED_2.P$1, U$1.SLEEVE, U$3.P$6, UNK0V0.MP
LEFT1: C204.2 (-), C204.B2 (-), PCB1.A0, R208.2, R208.2A (2), U1.1 (OUT)
LEFT2: C304.2 (-), C304.B2 (-), PCB1.A3, R408.2, R408.2A (2), U2.1 (OUT)
unnamed: C103.+, MAX1044.P$2 (C+)
unnamed: C103.-, MAX1044.P$4 (C-)
unnamed: C204.1 (+), C204.A1 (+), C404.-, C404.-VE (-), R208.1, R208.1A (1), U1.2 (IN-)
unnamed: C403.-, C403.-VE (-), R206.1, R206.1A (1), U1.3 (IN+)
unnamed: PCB1.A5, POT_A5.P$2 (WIPER)
unnamed: LEFT_IN0.+, LEFT_IN1.P$1, R204.2, R204.2A (2)
unnamed: LEFT_IN0.-, LEFT_IN1.P$2, R202.2, R202.2A (2)
unnamed: C201.1 (+), C201.A1 (+), C402.-, C402.-VE (-), R207.1, R207.1A (1), U1.6 (IN-)
unnamed: C401.-, C401.-VE (-), R205.1, R205.1A (1), U1.5 (IN+)
unnamed: PCB1.D3, R303.1, R303.1A (1)
unnamed: R203.2, R203.2A (2), RIGHT_IN0.+, RIGHT_IN1.P$1
unnamed: R201.2, R201.2A (2), RIGHT_IN0.-, RIGHT_IN1.P$2
unnamed: PCB1.D2, R304.1, R304.1A (1)
unnamed: LED_2.P$2, R103.1, R103.1A (1), R303.2, R303.2A (2), RIGHT_LED0.-
unnamed: LED_1.P$2, LEFT_LED0.-, R104.1, R104.1A (1), R304.2, R304.2A (2)
unnamed: PCB1.A2, POT_A4.P$2 (WIPER)
unnamed: C304.1 (+), C304.A1 (+), C503.-, C503.-VE (-), R408.1, R408.1A (1), U2.2 (IN-)
unnamed: C504.-, C504.-VE (-), R406.1, R406.1A (1), U2.3 (IN+)
unnamed: LED1.A, R1.2, R1.2A (2)
unnamed: R102.1, R102.1A (1), R301.2, R301.2A (2), R_LED_2.P$2
unnamed: C301.1 (+), C301.A1 (+), C501.-, C501.-VE (-), R407.1, R407.1A (1), U2.6 (IN-)
unnamed: C502.-, C502.-VE (-), R403.1, R403.1A (1), U2.5 (IN+)
unnamed: R401.2, R401.2A (2), RIGHT_IN_2.P$1
unnamed: L_LED_2.P$2, R101.1, R101.1A (1), R302.2, R302.2A (2)
unnamed: PCB1.D4, R302.1, R302.1A (1)
unnamed: PCB1.D5, R301.1, R301.1A (1)
unnamed: C501.+, C501.+VE (+), R401.1, R401.1A (1)
unnamed: C502.+, C502.+VE (+), R402.1, R402.1A (1)
unnamed: C503.+, C503.+VE (+), R504.1, R504.1A (1)
unnamed: C504.+, C504.+VE (+), R405.1, R405.1A (1)
unnamed: C401.+, C401.+VE (+), R201.1, R201.1A (1)
unnamed: LEFT_IN_2.P$1, R504.2, R504.2A (2)
unnamed: LEFT_IN_2.P$2, R405.2, R405.2A (2)
unnamed: C402.+, C402.+VE (+), R203.1, R203.1A (1)
unnamed: R402.2, R402.2A (2), RIGHT_IN_2.P$2
unnamed: C404.+, C404.+VE (+), R204.1, R204.1A (1)
unnamed: C403.+, C403.+VE (+), R202.1, R202.1A (1)
RIGHT1: C201.2 (-), C201.B2 (-), PCB1.A1, R207.2, R207.2A (2), U1.7 (OUT)
RIGHT2: C301.2 (-), C301.B2 (-), PCB1.A4, R407.2, R407.2A (2), U2.7 (OUT)
VCC: C101.+, C203.2 (-), C203.B2 (-), C303.2 (-), C303.B2 (-), LED_1.P$3, LED_2.P$3, LEFT_LED0.S, L_LED_2.P$3, MAX1044.P$1 (BST), MAX1044.P$8 (V+), PCB1.VIN, POT_A4.P$1 (CCW), POT_A5.P$1 (CCW), POWER_IN0.P$1, R1.1, R1.1A (1), RIGHT_LED0.S, R_LED_2.P$3, SW6.P$3 (2), SW6.P$4 (2), SW7.P$3 (2), SW7.P$4 (2), SW8.P$3 (2), SW8.P$4 (2), SW9.P$3 (2), SW9.P$4 (2), U1.8 (VCC), U2.8 (VCC), U$1.TIP, U$3.P$5, UNK5V0.MP
VEE: C102.-, C202.1 (+), C202.A1 (+), C302.1 (+), C302.A1 (+), MAX1044.P$5 (OUT), U1.4 (VEE), U2.4 (VEE)

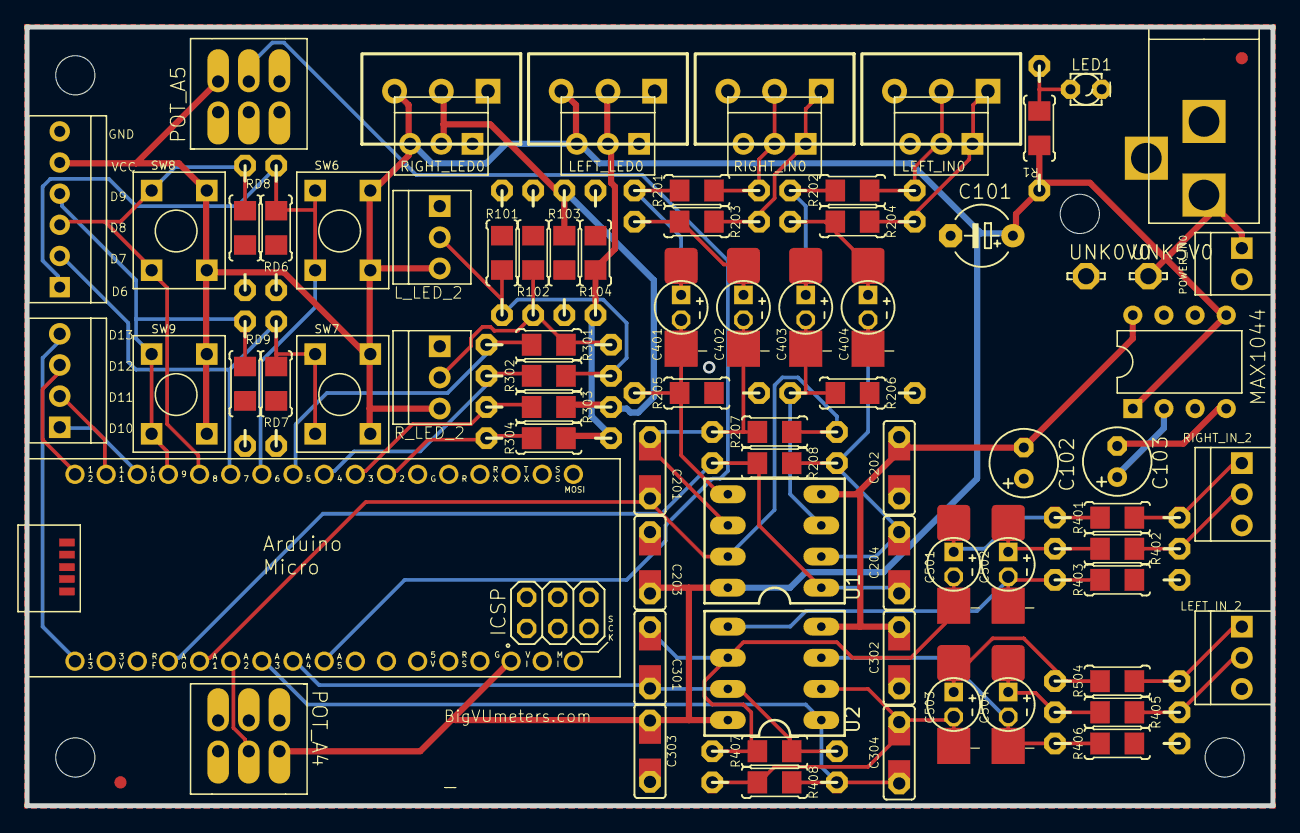
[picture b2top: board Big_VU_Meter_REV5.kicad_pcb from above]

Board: 2 copper layers, 101.6 x 63.5 mm, 84 parts (0 on the bottom side), 52 nets.

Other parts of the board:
UNK_HOLE_0: dummyfp0
UNK_HOLE_1: dummyfp1
UNK_HOLE_2: dummyfp2
UNK_HOLE_3: dummyfp3
